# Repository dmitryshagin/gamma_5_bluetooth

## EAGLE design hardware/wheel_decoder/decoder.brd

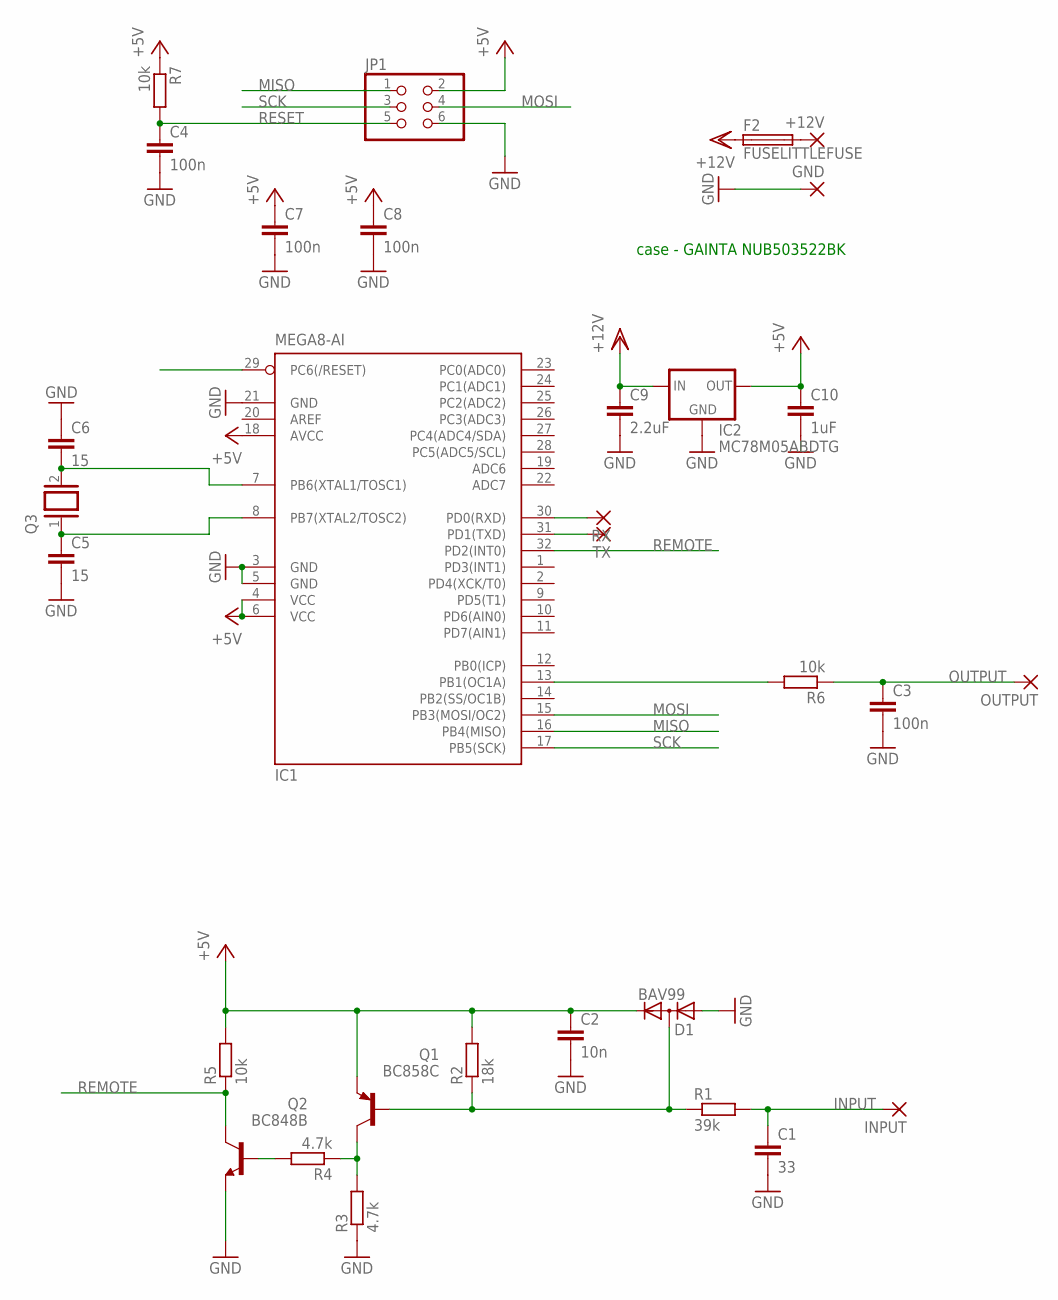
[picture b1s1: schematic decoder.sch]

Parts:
+12V: 3,81/1,4
C1: 33; C0603
C2: 10n; C0603
C3, C4, C7, C8: 100n; C0603
C5, C6: 15; C0603
C9: 2.2uF; C3225
C10: 1uF; C1206
D1: BAV99; SOT23
F2: FUSELITTLEFUSE; LITTLEFUSE
GND: 3,81/1,4
IC1: MEGA8-AI; TQFP32-08
IC2: MC78M05ABDTG; DPACK
INPUT: 2,54/1,1
JP1: PINHD-2X3; 2X03
OUTPUT: 2,54/1,1
Q1: BC858C; SOT23-BEC
Q2: BC848B; SOT23
Q3: XTAL/S; QS
R1: 39k; R0603
R2: 18k; R0603
R3, R4: 4.7k; R0603
R5, R6, R7: 10k; R0603
RX: 1,6/0,8
TX: 1,6/0,8

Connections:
GND: C1.2, C2.2, C3.2, C4.2, C5.2, C6.1, C7.2, C8.2, C9.2, C10.2, D1.1 (A), GND.1, IC1.3 (GND), IC1.5 (GND), IC1.21 (GND), IC2.4 (GND), JP1.6, Q2.2 (E), R3.1
INPUT: C1.1, INPUT.1, R1.2
MISO: IC1.16 (PB4(MISO)), JP1.1
MOSI: IC1.15 (PB3(MOSI/OC2)), JP1.4
unnamed: D1.3 (AC), Q1.B, R1.1, R2.1
unnamed: +12V.1, F2.2
unnamed: Q1.C, R3.2, R4.1
unnamed: Q2.1 (B), R4.2
unnamed: IC1.30 (PD0(RXD)), RX.1
unnamed: IC1.31 (PD1(TXD)), TX.1
unnamed: IC1.13 (PB1(OC1A)), R6.2
unnamed: C6.2, IC1.7 (PB6(XTAL1/TOSC1)), Q3.2
unnamed: C5.1, IC1.8 (PB7(XTAL2/TOSC2)), Q3.1
OUTPUT: C3.1, OUTPUT.1, R6.1
REMOTE: IC1.32 (PD2(INT0)), Q2.3 (C), R5.1
RESET: C4.1, IC1.29 (PC6(/RESET)), JP1.5, R7.2
SCK: IC1.17 (PB5(SCK)), JP1.3
VCC: C2.1, C7.1, C8.1, C10.1, D1.2 (C), IC1.4 (VCC), IC1.6 (VCC), IC1.18 (AVCC), IC2.3 (OUT), JP1.2, Q1.E, R2.2, R5.2, R7.1
VDD: C9.1, F2.1, IC2.1 (IN)

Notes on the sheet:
case - GAINTA NUB503522BK

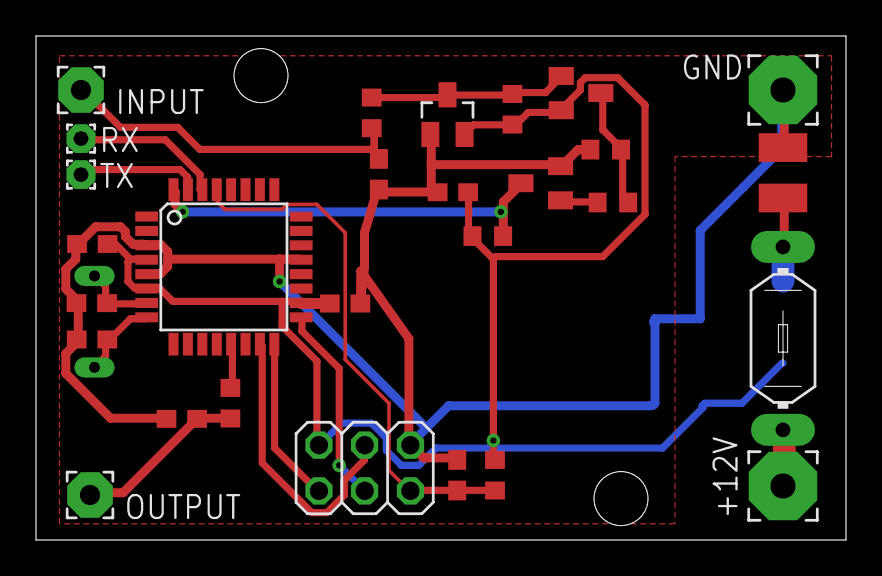
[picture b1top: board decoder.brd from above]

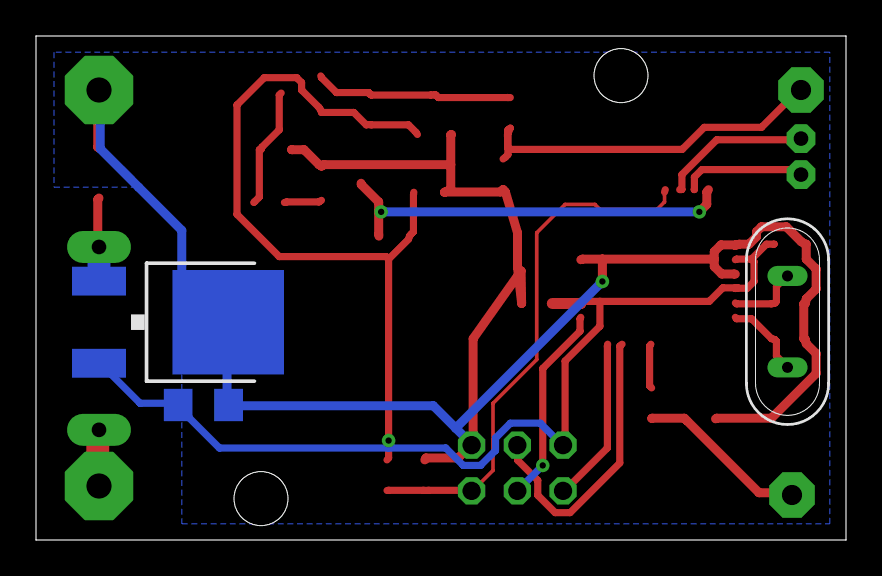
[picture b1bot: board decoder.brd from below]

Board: 2 copper layers, 45.0 x 28.0 mm, 31 parts (3 on the bottom side), 19 nets.

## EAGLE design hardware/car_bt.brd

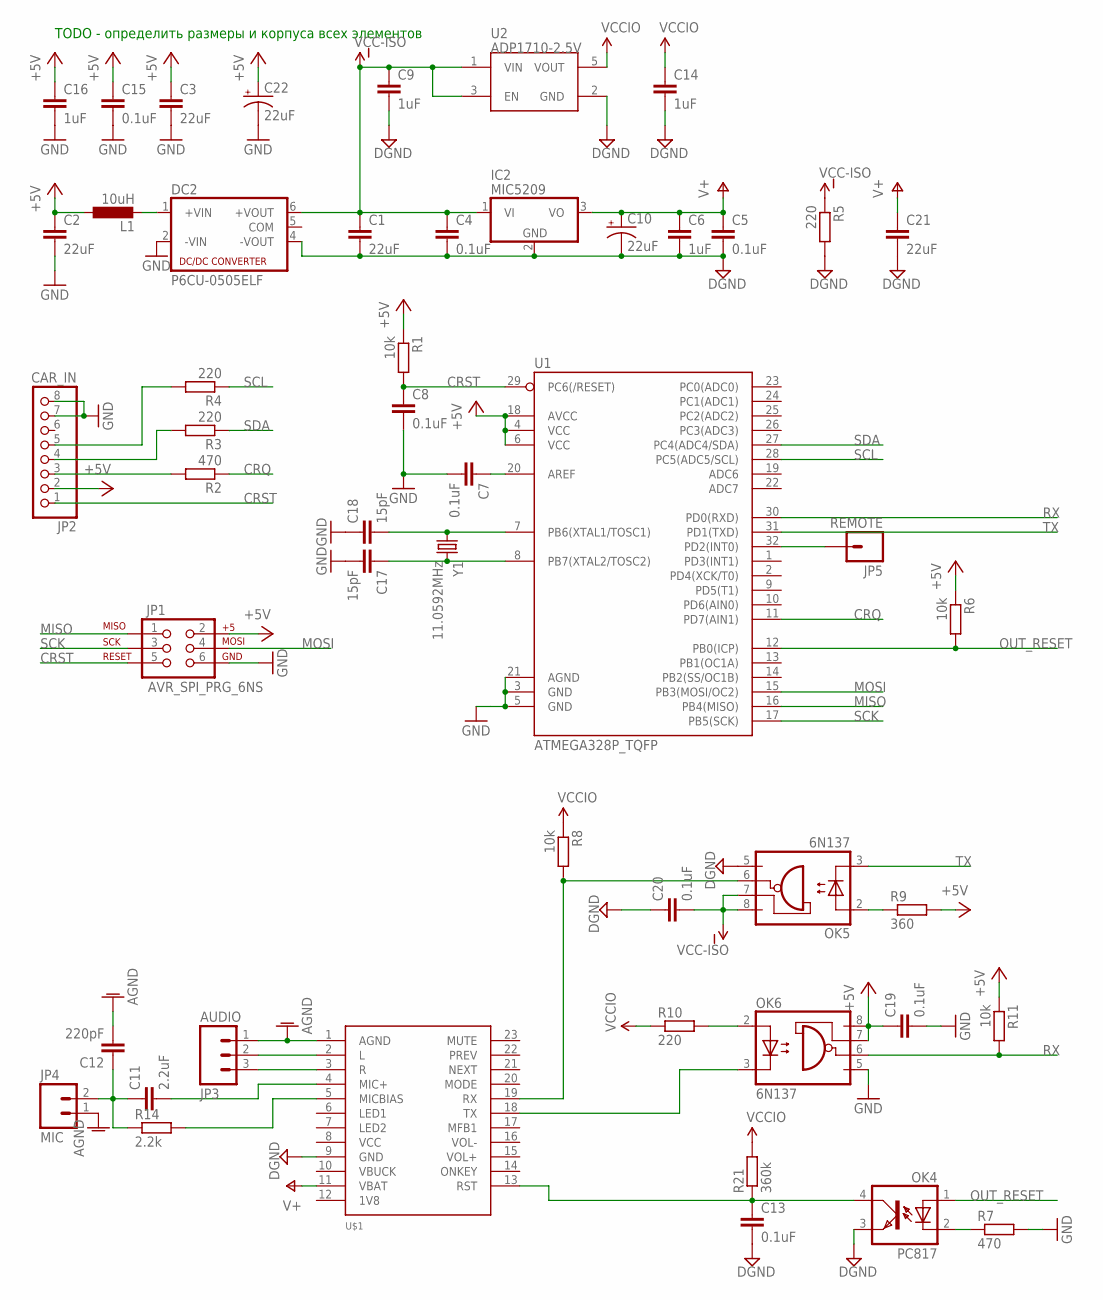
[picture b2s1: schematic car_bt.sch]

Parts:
C1, C2, C3, C21: 22uF; C1206
C4, C5, C7, C8, C13, C15, C19, C20: 0.1uF; C0805
C6, C9, C14, C16: 1uF; C0805
C10, C22: 22uF; EIA3528
C11: 2.2uF; C0805
C12: 220pF; C0805
C17, C18: 15pF; C0805
DC2: P6CU-0505ELF; NMA
IC2: MIC5209; SOT223
JP1: AVR_SPI_PRG_6NS; 2X3-NS
JP2: CAR_IN; 1X08/90
JP3: AUDIO; MOLEX-1X3
JP4: MIC; MOLEX-1X2_LOCK
JP5: REMOTE; 1X01_LONGPAD
L1: 10uH; L3216C
OK4: PC817; DIL04
OK5, OK6: 6N137; DIL08
R1, R6, R8, R11: 10k; R0805
R2, R7: 470; R0805
R3, R4, R5: 220; R0805
R9: 360; R0805
R10: 220; R1206
R14: 2.2k; R0805
R21: 360k; R0805
U1: ATMEGA328P_TQFP; TQFP32-08
U2: ADP1710-2.5V; SOT23-5
U$1: XS3868
Y1: 11.0592MHz; HC49U-V

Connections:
+5V: C2.1, C3.1, C15.1, C16.1, C19.1, C22.A (+), JP1.2, JP2.2, L1.1, OK6.7 (VE), OK6.8 (VCC), R1.1, R6.1, R9.2, R11.1, U1.4 (VCC), U1.6 (VCC), U1.18 (AVCC)
AGND: C12.2, JP3.1, JP4.1, U$1.1 (AGND)
CRQ: R2.1, U1.11 (PD7(AIN1))
CRST: C8.1, JP1.5, JP2.1, R1.2, U1.29 (PC6(/RESET))
DGND: C1.2, C4.2, C5.2, C6.2, C9.2, C10.C (-), C13.2, C14.2, C20.1, C21.2, DC2.4 (-VOUT), IC2.2 (GND), OK4.3 (EMIT), OK5.5 (GND), R5.2, U2.2 (GND), U$1.9 (GND)
GND: C2.2, C3.2, C7.2, C8.2, C15.2, C16.2, C17.2, C18.1, C19.2, C22.C (-), DC2.2 (-VIN), JP1.6, JP2.7, JP2.8, OK6.5 (GND), R7.2, U1.3 (GND), U1.5 (GND), U1.21 (AGND)
MISO: JP1.1, U1.16 (PB4(MISO))
MOSI: JP1.4, U1.15 (PB3(MOSI/OC2))
unnamed: JP2.3, R2.2
unnamed: JP2.4, R3.2
unnamed: JP2.5, R4.2
unnamed: DC2.1 (+VIN), L1.2
unnamed: OK6.3 (C), U$1.18 (TX)
unnamed: C7.1, U1.20 (AREF)
unnamed: C11.1, C12.1, JP4.2, R14.1
unnamed: JP3.2, U$1.2 (L)
unnamed: JP3.3, U$1.3 (R)
unnamed: JP5.1, U1.32 (PD2(INT0))
unnamed: OK5.2 (A), R9.1
unnamed: C13.1, OK4.4 (COL), R21.1, U$1.13 (RST)
unnamed: C17.1, U1.8 (PB7(XTAL2/TOSC2)), Y1.2
unnamed: OK5.6 (VO), R8.2, U$1.19 (RX)
unnamed: OK6.2 (A), R10.2
unnamed: C18.2, U1.7 (PB6(XTAL1/TOSC1)), Y1.1
unnamed: OK4.2 (C), R7.1
unnamed: C11.2, U$1.4 (MIC+)
unnamed: R14.2, U$1.5 (MICBIAS)
OUT_RESET: OK4.1 (A), R6.2, U1.12 (PB0(ICP))
RX: OK6.6 (VO), R11.2, U1.30 (PD0(RXD))
SCK: JP1.3, U1.17 (PB5(SCK))
SCL: R4.1, U1.28 (PC5(ADC5/SCL))
SDA: R3.1, U1.27 (PC4(ADC4/SDA))
TX: OK5.3 (C), U1.31 (PD1(TXD))
V+: C5.1, C6.1, C10.A (+), C21.1, IC2.3 (VO), U$1.11 (VBAT)
VCC-ISO: C1.1, C4.1, C9.1, C20.2, DC2.6 (+VOUT), IC2.1 (VI), OK5.7 (VE), OK5.8 (VCC), R5.1, U2.1 (VIN), U2.3 (EN)
VCCIO: C14.1, R8.1, R10.1, R21.2, U2.5 (VOUT)

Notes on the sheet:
TODO - определить размеры и корпуса всех элементов

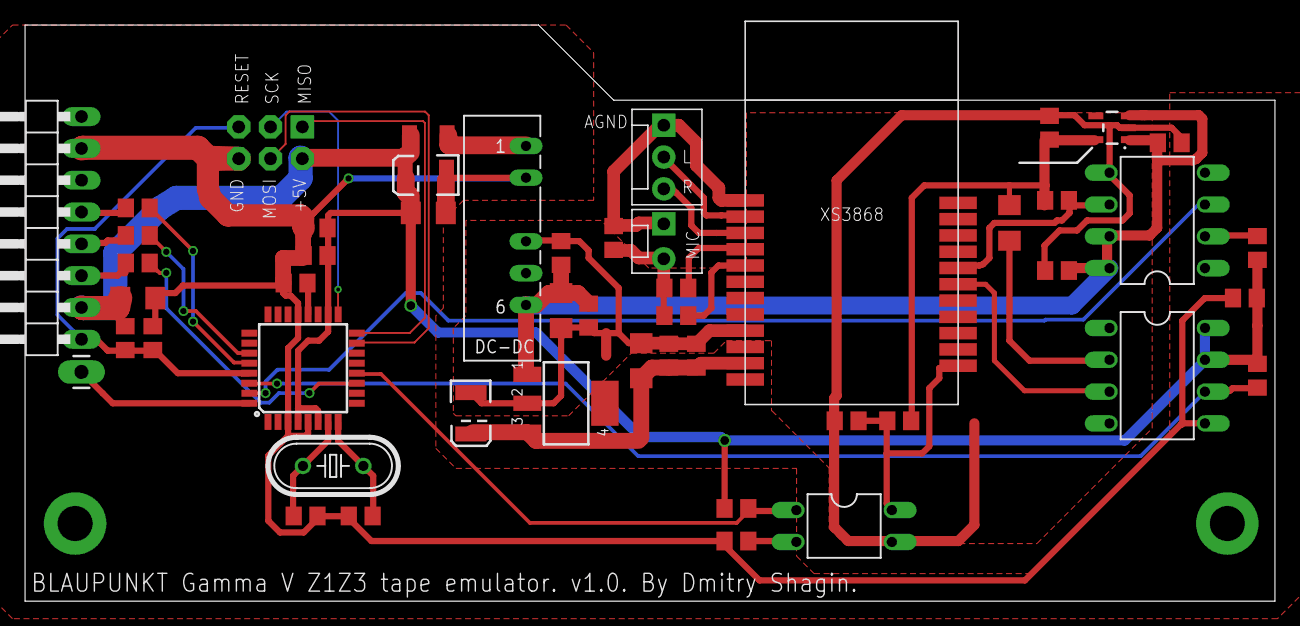
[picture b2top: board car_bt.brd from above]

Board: 2 copper layers, 99.8 x 46.0 mm, 50 parts (0 on the bottom side), 36 nets.

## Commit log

2016-05-13 selected components
2016-05-15 v 1.0 of hardware completed
2016-06-21 switched to uart
2017-07-10 Added wheel decoder
2017-08-14 Added PWM output to reciever
2018-05-13 Reciever now decodes to resistive load
2018-06-13 Added hex
2018-06-26 Added version for Arduino (9600 baud, 16Mhz crystal)
2019-03-16 Adding HEX
2020-02-12 Add partlist

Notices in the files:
parts and their libraries:
SparkFun-Connectors: Licensing: Creative Commons ShareAlike 4.0 International - https://creativecommons.org/licenses/by-sa/4.0
